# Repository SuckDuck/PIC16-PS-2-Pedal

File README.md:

# PIC16-PS/2-Pedal

This repository provides an implementation of the PS/2 keyboard protocol for the PIC16 microcontroller,
along with code and schematics for an [`Express Scribe`](https://www.nch.com.au/scribe/index.html)-compatible
transcription pedal. I used [`SDCC`](https://sourceforge.net/p/sdcc/wiki/Home/) as the compiler,
and an arduino nano with [`ZEPP`](https://github.com/battlecoder/zeppp/) as the programmer, so ensure both are 
properly installed on your system to use the provided Makefile 
(which, by the way, was borrowed from [here](https://github.com/diegoherranz/sdcc-examples)).

I also used [`PulseView`](https://sigrok.org/wiki/PulseView) extensively for debugging purposes with an arduino 
uno as a signal analyzer, thanks to [this](https://github.com/gillham/logic_analyzer/) project.
To create a proper development environment, I used the [`Embedded IDE`](https://em-ide.com/en/docs/getting-started/setup/)
vscode extension. So, for using or editing this repository or similar ones, it would be a good idea to check above links.

## Make instructions

1. Install `SDCC` and `ZEPP`.
2. Edit the Makefile:
    - Set `FAMILY` and `PROC` to match your PIC microcontroller.
    - Set `PORT` to the correct Arduino port (verify through the Arduino IDE).

3. Connect the Arduino to the PIC as per the `ZEPP` guide.
4. Run make upload in the directory where the Makefile is located.

## How to use it

The pedal has three shortcuts for working with `Express Scribe`. If it is pressed once, it triggers the `F9` key,
or the `F4` key, which are the default keys for play and pause in `Express Scribe`. If it is pressed and held, it
continuously triggers the `F7` key for rewind. Finally, if it is quickly double-pressed and then held, it 
triggers the `F8` key for fast forward. If you want to change those shortcuts just change the next lines for the
keys you want:
```
keyCode_t stop_f4    = SCAN_CODE_F4;
keyCode_t play_f9    = SCAN_CODE_F9;
keyCode_t rewind_f7  = SCAN_CODE_F7;
keyCode_t forward_f8 = SCAN_CODE_F8;
```
You can also completely change how the pedal work following the guide below.

The pedal does not require additional software to work with any PC or device, as it operates using the PS/2 
keyboard protocol. Therefore, if your PC has a PS/2 keyboard port, the pedal will function correctly. 
It can also work via USB if your PC supports PS/2 over USB with passive adapters; otherwise, 
you will need to purchase a proper adapter.

## How does it work
Very basically, the program starts with some configuration code. It sets up the `DATA` and `CLOCK` pins as outputs. 
If you want to change the pins, make sure to update the SWITCH_CLOCK() macro as well. Next, it configures the Timer2
registers; the only important value there is PR2. This code is designed to work with the PIC's 4MHz internal clock, 
so if you're using a faster oscillator, you should adjust this value to maintain a transmition frequency between 
10 and 16.7 kHz.
```
// --------- THE CODE RELATED TO PIN CONFIGURATION LOOKS LIKE THIS
#define CLOCK_TRIS        TRISBbits.TRISB0
#define CLOCK_READER_TRIS TRISBbits.TRISB1
#define DATA_TRIS         TRISBbits.TRISB2
#define DATA_READER_TRIS  TRISBbits.TRISB3

#define CLOCK             PORTBbits.RB0
#define CLOCK_READER      PORTBbits.RB1
#define DATA              PORTBbits.RB2
#define DATA_READER       PORTBbits.RB3
#define SWITCH_CLOCK() (PORTB ^= 1 << 0)

DATA_READER_TRIS = CLOCK_READER_TRIS = 1;
DATA_TRIS = CLOCK_TRIS = 0;
CLOCK = DATA = 0;

// --------- THE CODE RELATED TO TIMER2 CONFIGURATION LOOKS LIKE THIS
T2CONbits.TMR2ON = 1; // ENABLE TIMER2

// PRESCALER - POSTSCALER CONFIG
T2CONbits.T2CKPS0 = 1;
T2CONbits.T2CKPS1 = 0;
T2CONbits.TOUTPS0 = 0;
T2CONbits.TOUTPS1 = 0;
T2CONbits.TOUTPS2 = 0;
T2CONbits.TOUTPS3 = 0;

// SET START AND END POINT
TMR2 = 0;
PR2  = 9;
```

As you probably want to send key codes to the host as a keyboard, you can use the `sendCode()`
function with the key code you want to send as the first parameter. For the second parameter, 
use 0 if you plan to send more than one code; otherwise, use 1

You can find the complete list of key codes [here](https://web.archive.org/web/20060718084816if_/http://www.computer-engineering.org/ps2keyboard/scancodes2.html),
but it is already included in the [scan_codes_set2.h](./scan_codes_set2.h) file. 

Before sending a code, you first need to use the `formatKeyCode()` function over it to set it 
up for be transmitted first.

```
// THESE INITIAL CODES ARE NECESSARY FOR KEYBOARD INITIALIZATION
keyCode_t stp        = SCAN_CODE_SELF_TEST;
keyCode_t scs        = SCAN_CODE_SET_2;
keyCode_t echo       = SCAN_CODE_ECHO;
keyCode_t ack        = SCAN_CODE_ACK;
keyCode_t idMsb      = SCAN_CODE_IDMSB;
keyCode_t idLsb      = SCAN_CODE_IDLSB;
keyCode_t break_     = SCAN_CODE_BREAK;

// THEN YOUR CUSTOM CODES
keyCode_t space      = SCAN_CODE_SPACE;
formatKeyCode(&space); // <--- REPEAT THIS LINE FOR ALL THE ABOVE CODES

// FOR A KEY PRESS
sendCode(space,1);

// FOR A KEY RELEASE
sendCode(break_,0);
sendCode(space,1);
```

Therefore, the program should consist of a continuous loop that checks if the host wants to 
send a command. If so, it should include a block that reads and manages the response. 
For example:
```
uint8_t command = 0;
uint8_t lastCommand = 0;
keyCode_t* lastKeyCode = &stp;
sendCode(stp,1);

while(1){
    // CHECK IF THERE IS A COMMAND TO READ
    if(CLOCK_READER == 0 && DATA_READER == 0){
        lastCommand = command;
        command = readCommand();
        while(CLOCK_READER == 0); //WAITS UNTIL HOST RELEASE'S CLOCK LINE
        switch(command){

            case COMMAND_READID:
            sendCode(ack,0);
            sendCode(idMsb,0);
            sendCode(idLsb,1);
            break;

            case COMMAND_ECHO:
            sendCode(echo,1);
            break;

            case COMMAND_RESEND:
            sendCode(*lastKeyCode,1);
            break;

            case COMMAND_RESET:
            sendCode(ack,0);
            sendCode(stp,1);
            break;

            default:
            sendCode(ack,1);
            if(lastCommand == COMMAND_SET_SCAN_CODE && command == 0){
                dummyDelay(105);
                sendCode(scs,1);
            }
            break;
        }
    }

    // --------- YOUR CODE HERE
}
```

These are the basic commands that a keyboard should respond to. If you want to add more or modify the behavior of 
the program after responding to a particular command, feel free to do so, but make sure to leave this code functionality as
it is because it is defined by the protocol itself.

## External links and documentation
At last, here is the documentation that i based this project on:
- https://en.wikipedia.org/wiki/PS/2_port
- https://www.burtonsys.com/ps2_chapweske.htm
- https://web.archive.org/web/20060901070633if_/http://www.computer-engineering.org/ps2keyboard/
- https://wiki.osdev.org/PS/2_Keyboard

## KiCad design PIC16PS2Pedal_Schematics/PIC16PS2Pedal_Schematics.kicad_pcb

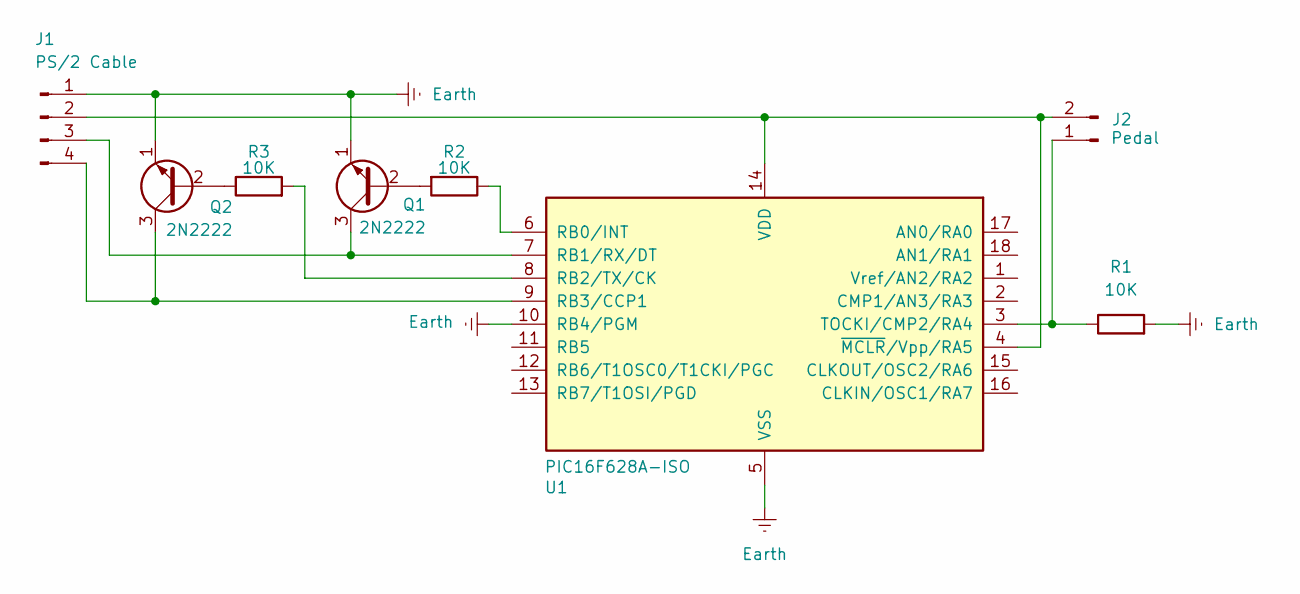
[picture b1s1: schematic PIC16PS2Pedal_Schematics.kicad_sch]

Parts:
J1: PS/2 Cable; FanPinHeader_1x04_P2.54mm_Vertical
J2: Pedal; LED_D2.0mm_W4.0mm_H2.8mm_FlatTop
Q1, Q2: 2N2222; TO-92
R1, R2, R3: 10K; R_Axial_DIN0207_L6.3mm_D2.5mm_P7.62mm_Horizontal
U1: PIC16F628A-ISO; DIP-18_W7.62mm_Socket

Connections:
Earth: J1.1, Q1.1 (E), Q2.1 (E), R1.2, U1.5 (VSS), U1.10 (RB4/PGM)
unnamed: J1.2, J2.2, U1.4 (~MCLR/Vpp/RA5), U1.14 (VDD)
unnamed: J1.3, Q1.3 (C), U1.7 (RB1/RX/DT)
unnamed: J1.4, Q2.3 (C), U1.9 (RB3/CCP1)
unnamed: J2.1, R1.1, U1.3 (TOCKI/CMP2/RA4)
unnamed: Q1.2 (B), R2.2
unnamed: Q2.2 (B), R3.1
unnamed: R2.1, U1.6 (RB0/INT)
unnamed: R3.2, U1.8 (RB2/TX/CK)

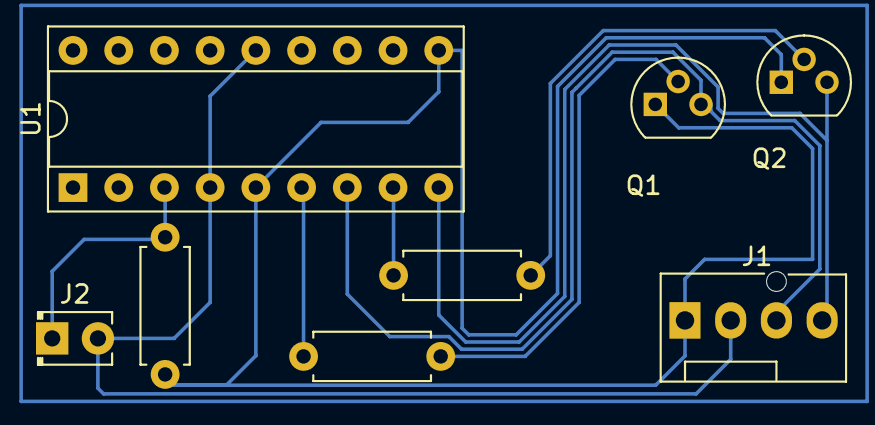
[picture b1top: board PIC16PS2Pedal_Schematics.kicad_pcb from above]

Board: 2 copper layers, 8 parts (0 on the bottom side), 9 nets.

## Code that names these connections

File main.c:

#define NO_BIT_DEFINES
#include <pic16f628a.h>
#include <stdint.h>
#include "scan_codes_set2.h"

__code uint16_t __at(_CONFIG) __configword = _INTOSC_OSC_NOCLKOUT & _WDTE_OFF & _LVP_OFF;
#define HIGH_IMPEDANCE    1
#define OUTPUT            0;

#define CLOCK_TRIS        TRISBbits.TRISB0
#define CLOCK_READER_TRIS TRISBbits.TRISB1
#define DATA_TRIS         TRISBbits.TRISB2
#define DATA_READER_TRIS  TRISBbits.TRISB3
#define PEDAL_TRIS        TRISAbits.TRISA4

#define CLOCK             PORTBbits.RB0
#define CLOCK_READER      PORTBbits.RB1
#define DATA              PORTBbits.RB2
#define DATA_READER       PORTBbits.RB3
#define PEDAL             PORTAbits.RA4

#define SWITCH_CLOCK() (PORTB ^= 1 << 0)

void formatKeyCode(keyCode_t *code_p){
    *code_p <<= 1;             // ADD STARTBIT
    *code_p |= 0b110000000000; // ADD ENDBIT

    // ADD PARITY BIT (ODD PARITY)
    int onesCount = 0;
    for (int i = 0; i < 12; i++) {
        if ((*code_p >> i) & 1){
            onesCount++;
        }
    }

    if(onesCount % 2 == 0){
        *code_p |= 0b1000000000;
    }

    // INVERT EVERYTHING
    *code_p ^= 0b111111111111;

}

void dummyDelay(int cycles){
    for(int i=0; i<cycles; i++){
        __asm nop __endasm;
    }
}

void sendCode(keyCode_t keyCode, int bypassDelay){
    //WAIT UNTIL NEXT TIMER2 CYCLE
    DATA = 1;
    while (!PIR1bits.TMR2IF);
    PIR1bits.TMR2IF = 0;

    for (int i = 0; i < 22; i++) {

        while (!PIR1bits.TMR2IF){
            if (!CLOCK && CLOCK_READER == 0) {
                // HOST IS INHIBITING COMMUNICATION
                CLOCK = 0;
                DATA  = 0;
                return;
            }
        }
        
        PIR1bits.TMR2IF = 0;
        SWITCH_CLOCK();
                
        if(!CLOCK){
            keyCode >>= 1;
            DATA = keyCode & 1;
        }
        
    }

    if(bypassDelay) return;
    dummyDelay(105);
    return;
}

uint8_t readCommand(){
    //WAIT UNTIL HOST RELEASE CLOCK
    uint8_t onesCount = 0;
    uint8_t command = 0;

    //WAIT TO HOST RELEASE CLOCK LINE
    while(CLOCK_READER == 0);
    dummyDelay(5);

    //WAIT UNTIL NEXT TIMER2 CYCLE
    while (!PIR1bits.TMR2IF);
    PIR1bits.TMR2IF = 0;

    //8 BITS OF DATA
    for (int i = 0; i < 16; i++) {
        while (!PIR1bits.TMR2IF);
        PIR1bits.TMR2IF = 0;
        SWITCH_CLOCK();
        if(!CLOCK){
            command >>= 1;
            if(DATA_READER){
                onesCount ++;
                command |= 0b10000000;
            }
        }

    }

    //PARITY BIT
    while (!PIR1bits.TMR2IF);
    PIR1bits.TMR2IF = 0;
    SWITCH_CLOCK();

    while (!PIR1bits.TMR2IF);
    PIR1bits.TMR2IF = 0;
    SWITCH_CLOCK();
    onesCount += DATA_READER;

    //STOP BIT
    while (!PIR1bits.TMR2IF);
    PIR1bits.TMR2IF = 0;
    SWITCH_CLOCK();

    while (!PIR1bits.TMR2IF);
    PIR1bits.TMR2IF = 0;
    SWITCH_CLOCK();

    // ACK BIT
    DATA = 1;    
    while (!PIR1bits.TMR2IF);
    PIR1bits.TMR2IF = 0;
    SWITCH_CLOCK();

    while (!PIR1bits.TMR2IF);
    PIR1bits.TMR2IF = 0;
    DATA = 0;
    SWITCH_CLOCK();


    if(onesCount % 2 != 0){
        return command;
    }

    return 0;
}

void main(){
#pragma region // ------------------------------ PIN'S INITIALIZATION ----------------------------- //
    DATA_READER_TRIS = CLOCK_READER_TRIS = PEDAL_TRIS = HIGH_IMPEDANCE;
    DATA_TRIS = CLOCK_TRIS = OUTPUT;
    CLOCK = DATA = 0;
#pragma endregion

#pragma region // --------------------------------- TIMER2_CONFIG --------------------------------- //
    T2CONbits.TMR2ON = 1; // ENABLE TIMER2

    // PRESCALER - POSTSCALER CONFIG
    T2CONbits.T2CKPS0 = 1;
    T2CONbits.T2CKPS1 = 0;
    T2CONbits.TOUTPS0 = 0;
    T2CONbits.TOUTPS1 = 0;
    T2CONbits.TOUTPS2 = 0;
    T2CONbits.TOUTPS3 = 0;

    // SET START AND END POINT
    TMR2 = 0;
    PR2  = 9;
#pragma endregion

    keyCode_t stp        = SCAN_CODE_SELF_TEST;
    keyCode_t scs        = SCAN_CODE_SET_2;
    keyCode_t echo       = SCAN_CODE_ECHO;
    keyCode_t ack        = SCAN_CODE_ACK;
    keyCode_t idMsb      = SCAN_CODE_IDMSB;
    keyCode_t idLsb      = SCAN_CODE_IDLSB;
    keyCode_t break_     = SCAN_CODE_BREAK;

    keyCode_t stop_f4    = SCAN_CODE_F4;
    keyCode_t play_f9    = SCAN_CODE_F9;
    keyCode_t rewind_f7  = SCAN_CODE_F7;
    keyCode_t forward_f8 = SCAN_CODE_F8;

    formatKeyCode(&stp);
    formatKeyCode(&scs);
    formatKeyCode(&echo);
    formatKeyCode(&ack);
    formatKeyCode(&idMsb);
    formatKeyCode(&idLsb);

    formatKeyCode(&break_);
    formatKeyCode(&stop_f4);
    formatKeyCode(&play_f9);
    formatKeyCode(&rewind_f7);
    formatKeyCode(&forward_f8);

    sendCode(stp,0);
    uint8_t command = 0;
    uint8_t lastCommand = 0;
    keyCode_t* lastKeyCode = &stp;
    int playCycle = 0;

    uint16_t pedalHoldTime = 0;
    uint16_t pedalDobleClickTimer = 0;
    int pedalState = PEDAL_STATE_SINGLE_CLICK;

    while(1) {

        if(pedalDobleClickTimer > 1){
            pedalDobleClickTimer ++;
        }

        if(pedalDobleClickTimer >= 2000){
            pedalDobleClickTimer = 0;
            if(pedalState == PEDAL_STATE_SINGLE_CLICK){
                //------------------------------------------- SINGLE CLICK
                playCycle ^= 1;
                if(playCycle == 1){
                    sendCode(play_f9,0);
                    sendCode(break_,0);
                    sendCode(play_f9,0);
                }

                else{
                    sendCode(stop_f4,0);
                    sendCode(break_,0);
                    sendCode(stop_f4,0);
                }
                
            }
        }

        if (PEDAL == 1 && CLOCK_READER == 1) {

            if (pedalHoldTime > 5){
                if (pedalDobleClickTimer > 1){
                    //---------------------------------------- DOUBLE CLICK
                    pedalState = PEDAL_STATE_DOBLE_CLICK;
                    sendCode(forward_f8,0);
                    sendCode(break_,0);
                    sendCode(forward_f8,0);
                }
                
                if (pedalDobleClickTimer == 0){
                    pedalDobleClickTimer = 1;
                }
            }

            if(pedalHoldTime < 3000) pedalHoldTime ++;
            if (pedalHoldTime == 3000 && (pedalState == PEDAL_STATE_SINGLE_CLICK || pedalState == PEDAL_STATE_HOLD_CLICK)){
                //--------------------------------------------- HOLD CLICK
                pedalState = PEDAL_STATE_HOLD_CLICK;
                sendCode(rewind_f7,0);
                sendCode(break_,0);
                sendCode(rewind_f7,0);
            }

        }

        if (PEDAL == 0){
            
            if(pedalHoldTime > 5){
                switch (pedalState){
                    case PEDAL_STATE_SINGLE_CLICK:
                    if(pedalDobleClickTimer == 1){
                        pedalDobleClickTimer = 2;
                    }
                    break;

                    //---------------------------------------- HOLD CLICK RELEASE
                    case PEDAL_STATE_HOLD_CLICK:
                    sendCode(break_,0);
                    sendCode(rewind_f7,0);
                    break;

                    //--------------------------------------- DOUBLE CLICK RELEASE
                    case PEDAL_STATE_DOBLE_CLICK:
                    pedalDobleClickTimer = 0;
                    sendCode(break_,0);
                    sendCode(forward_f8,0);

                    break;
                }                
            }
            
            pedalHoldTime = 0;
            pedalState = PEDAL_STATE_SINGLE_CLICK;
        }

        // CHECK IF THERE IS A COMMAND TO READ
        if(CLOCK_READER == 0 && DATA_READER == 0){
            lastCommand = command;
            command = readCommand();
            while(CLOCK_READER == 0); //WAITS UNTIL HOST RELEASE'S CLOCK LINE
            switch(command){

                case COMMAND_READID:
                sendCode(ack,0);
                sendCode(idMsb,0);
                sendCode(idLsb,1);
                break;

                case COMMAND_ECHO:
                sendCode(echo,1);
                break;

                case COMMAND_RESEND:
                sendCode(*lastKeyCode,1);
                break;

                case COMMAND_RESET:
                sendCode(ack,0);
                sendCode(stp,1);
                break;

                default:
                sendCode(ack,1);
                if(lastCommand == COMMAND_SET_SCAN_CODE && command == 0){
                    dummyDelay(105);
                    sendCode(scs,1);
                }

                break;

            }
        }
    }
}

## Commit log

2024-11-09 First commit.
2024-11-10 Update README, changes on the PCB layout
